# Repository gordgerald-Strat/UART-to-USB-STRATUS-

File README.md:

# UART-to-USB-STRATUS-
UART-to-USB breakout board designed for the soul purpose of being compatible with the small form factor air quality system( STRATUS)

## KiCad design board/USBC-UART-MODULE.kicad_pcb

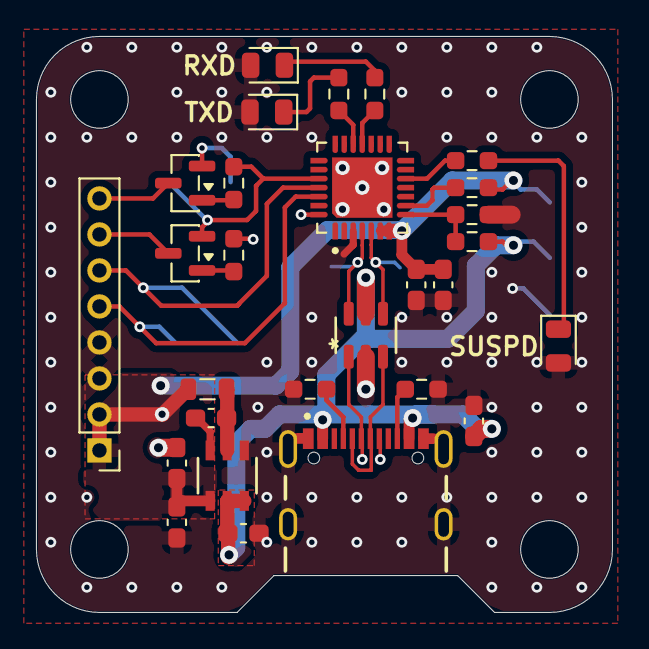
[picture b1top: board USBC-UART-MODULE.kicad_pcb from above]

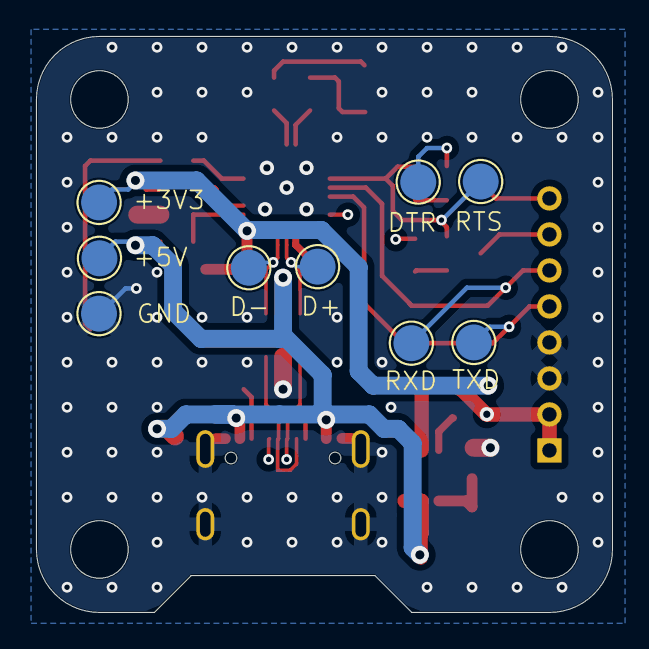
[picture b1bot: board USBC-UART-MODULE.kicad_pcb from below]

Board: 4 copper layers, 32.0 x 32.0 mm, 41 parts (9 on the bottom side), 27 nets.

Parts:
+3V3, +5V1: TestPoint; TestPoint_Pad_D2.0mm
Bottem1, Bottem3: MountingHole; MountingHole_3.2mm_M3
C3, C6: 100n; C_0603_1608Metric_Pad1.08x0.95mm_HandSolder
C4, C5, C18: 22u; C_0603_1608Metric_Pad1.08x0.95mm_HandSolder
C7, C19: 4u7; C_0603_1608Metric_Pad1.08x0.95mm_HandSolder
D3, D4, D5: RED; LED_0805_2012Metric
D+1: TestPoint; TestPoint_Pad_D2.0mm
D-1: TestPoint; TestPoint_Pad_D2.0mm
DTS1: TestPoint; TestPoint_Pad_D2.0mm
GND1: TestPoint; TestPoint_Pad_D2.0mm
J1: USBC; GCT_USB4105-GF-A-120
J2: Conn_01x08_Pin; PinHeader_1x08_P2.00mm_Vertical
L1: 4.7u; L_0805_2012Metric
Q2, Q3: SS8050; SOT-23
R1, R2: 5k1; R_0603_1608Metric_Pad0.98x0.95mm_HandSolder
R3, R5, R12, R13: 20k; R_0603_1608Metric_Pad0.98x0.95mm_HandSolder
R4: 47k; R_0603_1608Metric_Pad0.98x0.95mm_HandSolder
R17, R18, R19: 330; R_0603_1608Metric_Pad0.98x0.95mm_HandSolder
RTS1: TestPoint; TestPoint_Pad_D2.0mm
RXD1: TestPoint; TestPoint_Pad_D2.0mm
TXD1: TestPoint; TestPoint_Pad_D2.0mm
Top1, Top3: MountingHole; MountingHole_3.2mm_M3
U2: USB-PROT; TSOP-6_ONS-M
U3: BUCK_CONV; TSOT26_DIO-M
U4: USB-UART; IC_CP2102N-A02-GQFN28R

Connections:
+3V3: +3V3.1 (1_1), C4.1, C5.1, C6.1, C7.1, J2.1, J2.2, L1.2, R5.2, U3.1 (FB), U4.6 (VDD), U4.7 (VREGIN)
/BUCK_CONVERTOR/BOOT_STRAP: C3.1, U3.6 (BST)
/BUCK_CONVERTOR/FILTER: C3.2, L1.1, U3.5 (SW)
/USBC_INTERFACE/USBD+: J1.A6 (DP1), J1.B6 (DP2), U2.1
/USBC_INTERFACE/USBD-: J1.A7 (DN1), J1.B7 (DN2), U2.3
BOOT: J2.8, Q2.3 (C)
CHIP_PU: J2.7, Q3.3 (C)
DTR-UART: DTS1.1 (1_1), Q2.2 (E), R13.1, U4.28 (DTR)
GND: C4.2, C5.2, C6.2, C7.2, C18.1, C19.2, D3.2 (A), D4.2 (A), D5.2 (A), GND1.1 (1_1), J1.A1_B12 (GND), J1.B1_A12 (GND__1), J1.SH1 (SHELL_GND), J1.SH2 (SHELL_GND__1), J1.SH3 (SHELL_GND__2), J1.SH4 (SHELL_GND__3), J2.3, J2.4, R1.2, R2.2, R4.1, U2.2, U3.4 (GND), U4.3 (GND), U4.29 (EXP)
unnamed: D3.1 (K), R17.2
unnamed: D4.1 (K), R18.2
unnamed: D5.1 (K), R19.2
unnamed: J1.A5 (CC1), R1.1
unnamed: J1.B5 (CC2), R2.1
unnamed: Q2.1 (B), R12.2
unnamed: Q3.1 (B), R13.2
unnamed: D-1.1 (1_1), U2.6, U4.4 (D+)
unnamed: D+1.1 (1_1), U2.4, U4.5 (D-)
unnamed: R17.1, U4.19 (GPIO0_TXT)
unnamed: R18.1, U4.18 (GPIO1_RXT)
unnamed: R19.1, U4.12 (SUSPEND)
unnamed: R3.2, R4.2, U4.8 (VBUS)
unnamed: R5.1, U4.9 (~RST)
RTS-UART: Q3.2 (E), R12.1, RTS1.1 (1_1), U4.24 (RTS)
RXD-UART: J2.6, RXD1.1 (1_1), U4.25 (RXD)
TXD-UART: J2.5, TXD1.1 (1_1), U4.26 (TXD)
VBUS: +5V1.1 (1_1), C18.2, C19.1, J1.A4_B9 (VBUS), J1.B4_A9 (VBUS__1), R3.1, U2.5, U3.2 (EN), U3.3 (VIN)
